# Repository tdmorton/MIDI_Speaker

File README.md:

# MIDI Speaker

## Purpose

The purpose of this project is to build a simple host to receive MIDI commands over USB and output a synthesized sound to a speaker.

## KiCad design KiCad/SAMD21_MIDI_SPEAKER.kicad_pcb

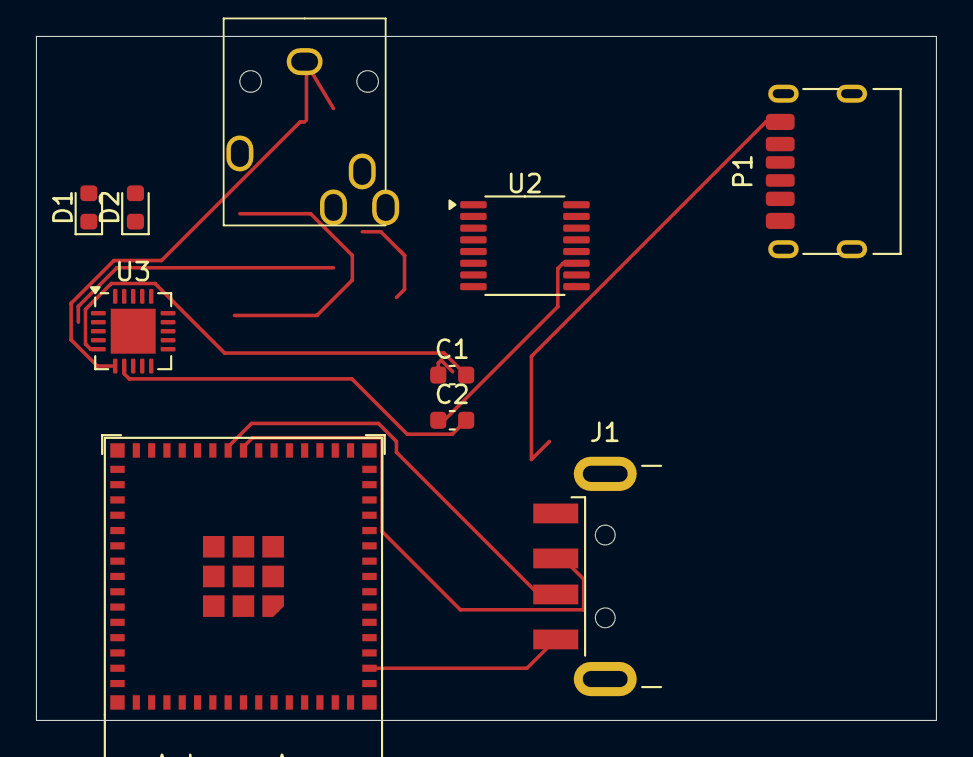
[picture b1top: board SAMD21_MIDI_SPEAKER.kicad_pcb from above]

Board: 2 copper layers, 50.0 x 38.0 mm, 10 parts (0 on the bottom side), 12 nets.

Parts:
C1, C2: C; C_0603_1608Metric
D1, D2: LED; D_0603_1608Metric
J1: USB_A; USB_A_CNCTech_1001-011-01101_Horizontal
J2: 54-00175
P1: USB_C_Plug_USB2.0; USB_C_Receptacle_HRO_TYPE-C-31-M-17
U2: TSSOP-16_4.4x5mm_P0.65mm
U3: PAM8019KGR; QFN-20-1EP_4x4mm_P0.5mm_EP2.5x2.5mm
U4: ESP32-S3-MINI-1

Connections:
+3.3V: U3.13 (VDD), U3.16 (VDD), U3.20 (VDD), U4.3 (3V3)
/AOUTL: C2.1, U2.11 (AOUTL)
/AOUTR: C1.1, U2.10 (AOUTR)
GND: J1.4 (GND), J1.5 (Shield), J2.1 (GROUND), U2.13 (VSS), U3.6 (GND), U3.18 (GND), U3.21 (GND), U4.1 (GND), U4.2 (GND), U4.42 (GND), U4.43 (GND), U4.46 (GND), U4.47 (GND), U4.48 (GND), U4.49 (GND), U4.50 (GND), U4.51 (GND), U4.52 (GND), U4.53 (GND), U4.54 (GND), U4.55 (GND), U4.56 (GND), U4.57 (GND), U4.58 (GND), U4.59 (GND), U4.60 (GND), U4.61 (GND), U4.62 (GND), U4.63 (GND), U4.64 (GND), U4.65 (GND)
unnamed: J1.3 (D+), U4.24 (GPIO20/U1CTS/ADC2_CH9/CLK_OUT1/USB_D+)
unnamed: J1.2 (D-), U4.23 (GPIO19/U1RTS/ADC2_CH8/CLK_OUT2/USB_D-)
unnamed: J2.3 (LEFT), U3.14 (HPLOUT)
unnamed: J2.2 (RIGHT), U3.2 (HPROUT)
unnamed: P1.A12 (GND), P1.B12 (GND)
unnamed: P1.A9 (VBUS), P1.B9 (VBUS)
unnamed: C2.2, U3.7 (LIN)
unnamed: C1.2, U3.5 (RIN)

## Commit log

2024-08-15 Adding Readme
2024-08-15 updated main.cpp to print to console
2024-08-15 another commit test
2024-08-19 simple pwm led script test
2024-08-21 Added block diagram and bom
2024-08-22 adding KiCad Project Files
2024-08-22 Updated schematic to include audio codec, battery charging circuit
2024-08-22 Changed folder name to reflect contents
2024-08-25 added samples and wavetable synth code
2024-08-25 added piano samples
